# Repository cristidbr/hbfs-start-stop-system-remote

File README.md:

# HBFS Robotics Start Stop System Remote

This is a premium remake of the original 
[p1rse](https://github.com/p1rse/robot-sumo-start-module) remote which 
is yet to be designed in KiCAD. 

This project improves upon the original in some few key areas:

- High quality Cherry MX ULP switches with RGB LEDs
- Removes pointing of the remote towards the robot
- High power OSRAM infrared LEDs
- STM32 microcontroller
- Power options ranging from Supercapacitors, Lithium cells and AAA batteries
- Charging via USB-C
- Zero switches, touch to power on, auto power off
- Lighweight and sleek design
- Lanyard compatible

In the style of the original remote, the BOM uses a carefully curated 
list of components that were singlehandedly selected for supply chain 
availability across the world, with one exception. Keycaps. Those remain 
challenging to source.

## Power Sourcing

As shipping batteries is difficult due to airline regulations, this remote 
uses an iPod nano 7th generation replacement battery P/Ns **616-0639** 
or **616-0640** as the preffered power source. At only 1.9mm thick, this 
Li-Ion battery is available in most places for around 20USD, while 
quantity purchases from places closer to manufacturing origins lower the 
cost of each cell down to around 5USD. As you can imagine, the total BOM 
cost of this remote sits way past its original partlist of 11USD with free 
PCBs.

Alternative power sources include Supercapacitors, AAA Batteries, and LiPo 
battery cells with JST PH connectors. These are available from the 
following suppliers:
- Supercapacitor [**ADCM-S05R5SA106RB**](https://octopart.com/part/abracon/ADCM-S05R5SA106RB)
- Adafruit LiPo P/Ns [**1578**](https://www.adafruit.com/product/1578), [**4236**](https://www.adafruit.com/product/4236), [**258**](https://www.adafruit.com/product/258)
- SparkFun LiPo P/Ns [**PRT-13854**](https://www.sparkfun.com/lithium-ion-battery-850mah.html), [**PRT-13851**](https://www.sparkfun.com/lithium-ion-battery-400mah.html)
- Akyga LiPo Cells such as the [**AKY0185**](https://www.tme.eu/en/details/aky-lp503040/rechargeable-batteries/akyga-battery/aky0185/) with wires soldered directly onto pads
- Triple AAA battery holder from Keystone [**2479**](https://www.digikey.com/en/products/detail/keystone-electronics/2479/303824)

The original design used two AA batteries. Since two standard AA batteries 
only sum up to 3V when brand new, there were not enough volts to push the 
infrared emitters very high. There were not enough amps as well, and the 
design used an electrolytic cap to overcome the high internal battery 
resistance limitations.

## Part Numbers

The following part numbers have been designated to each of the constructive 
variants. Contributions are welcome, and if someone finds a better way to 
power this remote, all 3D models are made available in the repo.

| P/N                            | Power Source          | Thickness | Charging | Unit Cost (10-pack) |
|--------------------------------|-----------------------|-----------|----------|---------------------|
| HBFS-STARTSTOP-REMOTE-THIN     | iPod Battery 616-0640 | 4MM       | USB-C    | TBD                 |
| HBFS-STARTSTOP-REMOTE-SUPERCAP | 5.5V Supercapacitor   | 15MM      | USB-C    | TBD                 |
| HBFS-STARTSTOP-REMOTE-JST      | JST PH LiPo Cell      | 8MM-15MM  | USB-C    | TBD                 |
| HBFS-STARTSTOP-REMOTE-LIPO     | Wired LiPo Cell       | 6MM       | USB-C    | TBD                 |
| HBFS-STARTSTOP-REMOTE-AAA      | AAA Batteries or NiMH | 14MM      | Cell     | TBD                 |

## Charging

The charging chip used is the TI's **BQ25170DSGR** featuring low quiescent 
current and up to 800mA of charging current. The current settings have to 
be sized for the appropriate cell used. 

## Contributions

HBFS Robotics contributes in the robotics space by dedicating its work to 
the **public domain**. We find ways.

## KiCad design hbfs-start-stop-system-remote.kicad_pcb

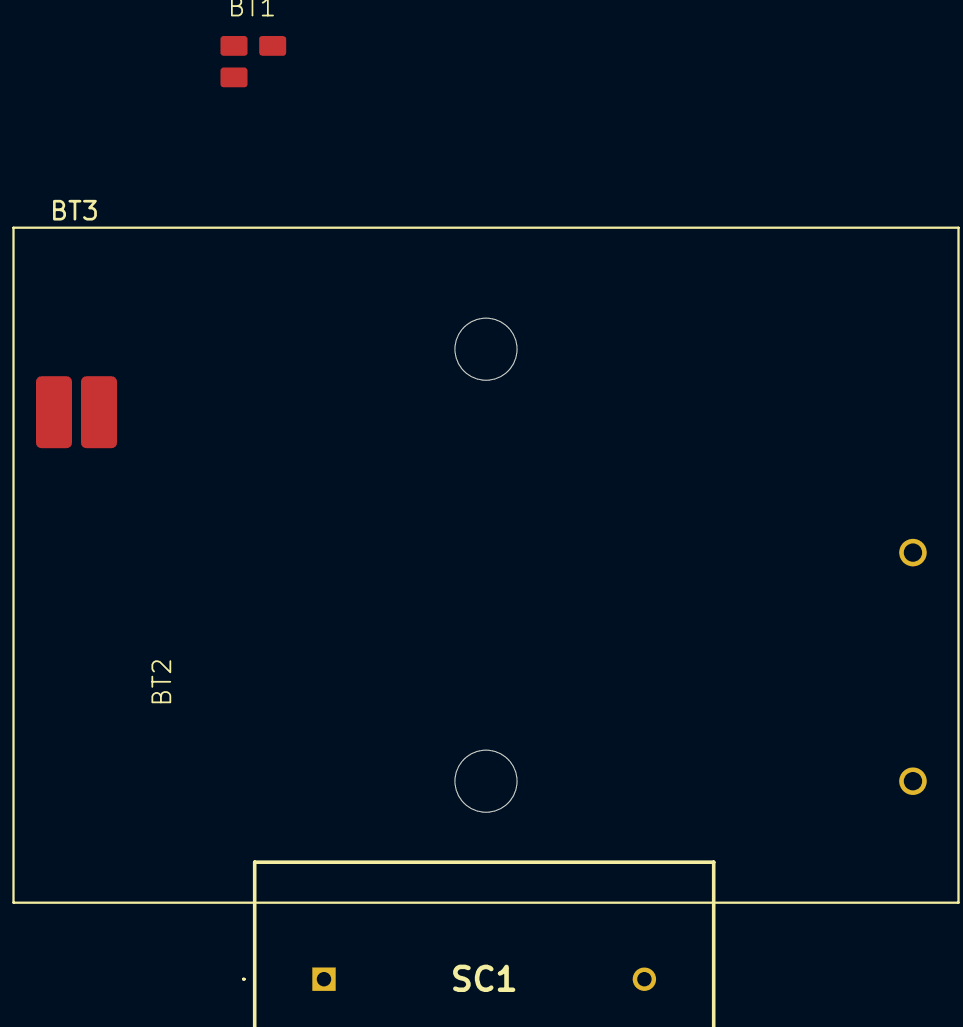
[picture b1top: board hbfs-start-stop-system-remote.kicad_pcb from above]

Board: 4 copper layers, 4 parts (0 on the bottom side), 2 nets, no tracks yet.

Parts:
BT1: 616-0640
BT2: AKY0185
BT3: 2479; BAT_2479
SC1: ADCM-S05R5SA106RB; ADCMS05R5SA106RB

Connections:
4V2BAT: BT1.2 (VBAT), BT2.2 (VBAT)
GND: BT1.3 (GND), BT2.1 (GND), BT3.N, SC1.2 (-)
